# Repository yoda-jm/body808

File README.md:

# Body808

Wearable body percussion: piezo sensors on the feet, chest, legs and hands turn
body hits into MIDI drum notes, sent by radio to a sampler that plays beatbox
sounds.

```
piezo pads ──> protection board ──> Arduino Mega ──> MIDI OUT ──> WIDI Master ~~BLE~~> PC ──> Hydrogen (beatbox kit)
(on the body)   (keeps the Mega alive)  (hit detection)   (DIN-5)    (Bluetooth MIDI)        (or USB cable for testing)
```

Each input plays one fixed sound. Where a pad goes on the body is up to you: plug
it into the input of the sound you want it to play.

| Pin | Sound | MIDI note | Suggested placement |
|-----|-------|-----------|---------------------|
| A0 | kick | 36 | foot (heel stomp) |
| A1 | snare | 38 | leg / thigh |
| A2 | hihat | 42 | other leg |
| A3 | bass | 35 | chest |
| A4 | clap | 39 | hand |
| A5 | openhat | 46 | other hand |

Notes follow the General MIDI drum map, so any drum sampler works out of the box.

> **Never wire a piezo directly to an analog pin.** A stomp produces tens of volts;
> the pin tolerates −0.5 … 5.5 V. Each input needs the 4-part protection circuit
> described in [docs/hardware.md](docs/hardware.md).

## Documentation

- [docs/hardware.md](docs/hardware.md): protection circuit, parts list, building and
  testing the board, making the pads, power and safety, MIDI DIN out
- [docs/parts.md](docs/parts.md): shopping list with links (amazon.fr searches)
- [docs/firmware.md](docs/firmware.md): output modes, pad settings, calibration, tuning
- [docs/sampler.md](docs/sampler.md): getting MIDI into the PC, Hydrogen setup, making
  the beatbox kit, latency
- [docs/simulation.md](docs/simulation.md): simulated hits through 7 board
  configurations (schematics, waveforms, detection), pros and cons of each, and the
  firmware's retrigger tuning
- [sim/README.md](sim/README.md): the simulation's models, sources and how to run it
- [hardware/shield/README.md](hardware/shield/README.md): the PCB that stacks on the Mega
  (8 jacks, MIDI OUT, knob): schematic, how to read the board, ordering it from JLCPCB

## Simulation

The protection board and the hit detector were simulated in ngspice before building
([docs/simulation.md](docs/simulation.md)): a piezo disc model with the real discs'
values, ~60 hits per board configuration from soft to 200 V, and the firmware's
detector replayed on every simulated pin voltage.

- **The pin is safe**: at most 131 µA into the Mega's own protection diodes on a 200 V
  hit (budget 0.5 mA), with the 1N4733A zener.
- **One note per hit**, in every hit shape and every configuration tried.
- **Velocity only works for small signals as built**: 0.2–3 V across the disc. If
  your pads give more (check with `CALIBRATE`), a 100 nF capacitor across the disc
  and R1 = 100 kΩ moves the window to 1–16 V.
- **Retrigger tuning**: `RETRIGGER_RATIO` 0.5 → 0.25 and `DECAY_US` 80 → 50 ms, so a
  soft hit right after a loud one is no longer lost, without ghost notes.

```
python3 sim/run.py        # sweeps: stress, tolerances, ringing, transfer
python3 sim/report.py     # docs/simulation.md figures, per configuration
python3 sim/tuning.py     # firmware retrigger settings
```

## Quick start

1. Build the protection board and **check it with a multimeter before connecting it**
   ([hardware.md](docs/hardware.md#check-before-plugging-into-the-mega)).
2. Upload with `CALIBRATE 1`, set each pad's `threshold`/`maxLevel` from the Serial
   Plotter ([firmware.md](docs/firmware.md#calibration-procedure)).
3. Upload with `CALIBRATE 0` and `MIDI_MODE_DISPLAY`, check hits in the Serial Monitor.
4. Switch to `MIDI_MODE_USB_SERIAL`, run the bridge, play GMRockKit in Hydrogen
   ([sampler.md](docs/sampler.md)).
5. Record beatbox samples, build the kit with `tools/make_hydrogen_kit.py`.
6. Switch to `MIDI_MODE_SERIAL`, plug the WIDI Master into the MIDI OUT socket, pair it
   with the PC ([sampler.md](docs/sampler.md#radio-cme-widi-master)), run on battery.

## Files

```
body808.ino                    firmware (Arduino Mega 2560)
tools/serial_midi_bridge.py    USB/radio serial port -> ALSA MIDI port
tools/make_hydrogen_kit.py     samples/ folder -> Hydrogen drumkit
sim/                           ngspice models, sweeps, firmware replay and tuning
docs/                          documentation and schematics (SVG)
hardware/shield/               KiCad shield PCB + schematic, generated by build_shield.py
attic/                         the original Blink/MIDI test sketch
```

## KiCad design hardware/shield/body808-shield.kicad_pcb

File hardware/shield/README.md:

# body808 shield

A board that plugs on top of the Arduino Mega 2560 and replaces the breadboard. It has
8 protected drum inputs on side-entry 3.5 mm jacks, the MIDI OUT socket for the WIDI
Master, and a flat connector for the sensitivity knob. It overhangs the Mega by 17 mm on
the digital-pin side, so that every connector sits on one edge and all cables leave on
the same side.

## How it stacks

Both boards stay the right way up: the shield sits on top of the Mega, and the pin
headers under it plug into the Mega's sockets. The jacks and the MIDI socket are on the
part that overhangs the Mega.

The second drawing shows the alternative with stackable headers on top, which would let
the factory solder everything in its cheaper one-sided service. In November 2026 JLCPCB
had no stackable header in stock, so the board keeps the headers underneath.
`stacking.py` draws this picture.

## Schematic

To print it, use [body808-shield-schematic.pdf](body808-shield-schematic.pdf). To open it in KiCad, open
`body808-shield.kicad_pro`: the schematic and the board are one KiCad project, linked
part by part. Every check (`make_fab.sh`) runs KiCad's schematic-parity test, which
fails if the board and the schematic disagree on a single part, value or connection.

## How to read the drawing

**Everything is on the top side**, ground included. The underside has no copper
except the pads of the through-hole parts. Every red line you see on top is a real
connection.

**Lanes:** each jack has its own lane, separated by white lines, laid out like its
schematic:

```
    JACK (on the edge)
      sleeve ●──────────┐
         tip ●──┐       │       right line = GND (from the jack's sleeve and switch pins)
      switch ●──┼───────┤
                ├─[1M]──┤       1M and the zener lie flat: from the signal line to GND
              [10k]     │
                ├[ZENER]┘
               [1k]
                │               left line = signal: tip -> 10k -> 1k
             to A0 ... A7 (header into the Mega)
```

**Ground is one line.** It leaves the Mega's GND pins (J1) at the bottom, runs to the
far left, goes up the left edge, then straight across the top through every jack's
sleeve pin, and on to the MIDI socket. Each lane's GND line drops straight down from it,
marked `GND`, and picks up the jack's switch pin on the way. The knob connector gets its
GND from J1 too, along the bottom edge under the A0–A7 pins.

**When nothing is plugged in:** the jack's switch connects the tip to GND, so an empty
input reads 0 and plays nothing.

**The right part of the board:**

- the MIDI socket in the top-right corner, with R1 and R2 under it;
- 5V coming down from the Mega's 5V pins (J7) to the knob connector at the lower right;
- the two test pads below the knob, 5V and GND.

**Labels:** every line has a short label printed next to it (`GND`, `5V`, `TX1`, `A8`,
`220`, the MIDI pin numbers), instead of a legend block. The title is `body808 v1`.

**What goes into the Mega:** only the pins that carry something.

| Header | Pins used | For |
|--------|-----------|-----|
| J1 (POWER) | GND | ground |
| J3 (A0–A7) | all 8 | one per lane |
| J5 (A8–A15) | A8 | knob |
| J6 (comms) | TX1 (pin 18) | MIDI |
| J7 (2 pins at the end of the 2×18 header) | 5V | MIDI and knob |

The other pins of J1, J5 and J6 are only there to hold the shield and aren't connected.

## Connectors

| Ref | What | Wiring |
|-----|------|--------|
| J21–J28 | `JACK1`–`JACK8` (PJ-316 mono jacks) | → A0 … A7. Tip (T) = piezo red, sleeve (S) = GND, switch (TN) = GND |
| J10 | MIDI OUT (DIN-5, CUI SDS-50J) | pin 4 → R1 220 Ω → 5V, pin 5 → R2 220 Ω → TX1, pin 2 + shield → GND, pins 1 and 3 unused |
| J11 | `KNOB` (flat JST-XH, 3 pins) | GND / 5V / A8, as printed next to it |
| TP1, TP2 | Test pads, bottom right | 5V and GND, for a multimeter |

**MIDI uses only 3 of the 5 pins**, which is the MIDI standard. The WIDI Master takes
its power from pin 4 (5V through 220 Ω) and pin 2 (GND), so it needs no other supply.

**Each lane** is the protection circuit from [docs/hardware.md](../../docs/hardware.md):

| Part | Value | Position in the lane |
|------|-------|----------------------|
| R1 | 1 MΩ | flat, signal line to GND line |
| R2 | 10 kΩ | in the signal line |
| D1 | 5.1 V zener, 1SMA4733A | flat, cathode band on the signal line |
| R3 | 1 kΩ | in the signal line, then to the Mega pin |

1SMA4733A is the SMD version of the 1 W 1N4733A that the simulation favours.

If real pads turn out to give more than ~3 V
([docs/simulation.md](../../docs/simulation.md)), the 100 nF capacitor can go across
the piezo inside the pad. That's electrically the same place, so the board doesn't need
a spot for it.

**Clearances:**

- **Piezo inputs:** the line from each jack tip to its 10k sees the piezo's spikes
  (50–200 V, well under a millisecond). It keeps at least 0.8 mm from GND copper,
  including the jack's own GND pins.
- **Other tracks:** at least 0.5 mm apart (A0–A7 lines, 5V and TX1).
- **Board edge:** at least 0.75 mm from copper.

**Nothing pokes into the Mega.** Over the Mega's USB socket, power jack and ICSP header
there are no solder joints and no bottom copper. Over the Mega, only the pin headers
and the knob connector's 3 pins go through the board, and nothing tall sits under the
knob connector. The jacks and the MIDI socket are on the overhang.

## Order it (JLCPCB)

The BOM uses LCSC part numbers, so JLCPCB can assemble the board. `fab/` holds the three
files to upload, nothing else.

1. On jlcpcb.com, upload `fab/gerbers-jlcpcb.zip`. The defaults are fine (2 layers,
   1.6 mm). Pick **lead-free HASL**, since the board will be worn.
2. Enable **PCB Assembly**, **Economic**, top side, 2 or 5 boards. Upload
   `fab/bom-jlcpcb.csv` and `fab/cpl-jlcpcb.csv`.
3. The files ask the factory to solder **everything on the top**: the 34 resistors and
   zeners, the 8 jacks, the MIDI socket and the knob connector. The **pin headers are
   left out on purpose**: they sit on the bottom, and a bottom-side part moves the
   order to double-sided assembly (about $60 more). Solder them yourself (see below).
4. **Check the placement preview** before paying:
   - **Zeners D101 … D801:** each lies flat across its lane. The cathode band must be
     on the **left, on the signal line**. A reversed zener gives no protection.
   - **Jacks and MIDI socket:** facing out of the top edge.
   - **Knob connector:** opening toward the right edge.

   Rotate anything that looks wrong in the preview: rotation conventions differ between
   KiCad and JLCPCB.

**Pin headers, by hand:** 4 strips of 8 (J1, J3, J5, J6) and one of 2 (J7, cut from a
strip), 2.54 mm male, plastic **under** the board, soldered from the top. The easy way
to get them straight: push them into the Mega's sockets, put the shield on top,
solder, then lift it off. LCSC C492407 is a strip of 8.

**What it costs** (researched 2026-11-05, USD before shipping and VAT):

| | 2 boards | 5 boards |
|---|---|---|
| Factory solders everything on top (the files as they are) | ~$40 | ~$63 |
| Factory solders only the 34 small parts, you buy and solder the rest | ~$36 | ~$57 |
| Bare boards only, no parts | ~$5 for 5 | |

- **Where it goes:** the MIDI socket ($4.27 each) and the jacks ($0.22 each) are most
  of the parts cost. The assembly setup is about $8 and the stencil $1.50 per order,
  whatever the quantity.
- **Shipping to France:** about $7–9 for the slow options, about $30 by DHL.
- **VAT and duty:** French VAT (20%) is added at checkout. Since July 2026 each EU
  parcel also pays a flat €3 customs duty per goods category, plus a few euros of handling fees.
  JLCPCB collects that at checkout on some shipping routes; on others it's charged on
  delivery.
- **The famous "$2 for 5 boards"** is now only in JLCPCB's desktop app, which runs on
  Windows and macOS (not Linux); on the website it's about $4.
- **Stock:** the MIDI socket (C6216157) and the Kinghelm jack (C5123139) were low (138
  and 272 left). If the jack runs out, the CAX PJ-316 (C50176628) is a drop-in
  replacement.

Bare boards (no assembly) can also come from PCBWay or Aisler (made in Germany, no
customs for the EU) with the same Gerber zip. You then solder the 1206 parts by hand;
that size is easy with a fine tip.

Part numbers, in case one is out of stock: [build_shield.py](build_shield.py) (`LCSC = {...}`).
The jack has a drop-in second source, CAX PJ-316 (C50176628).

## Before plugging it into the Mega

- Put a piece of Kapton or electrical tape on top of the Mega's USB socket. It reaches
  the underside of the shield.
- Do the multimeter checks from
  [docs/hardware.md](../../docs/hardware.md#check-before-plugging-into-the-mega) on each
  lane, measuring at the jack (tip) and the A0 … A7 header pins.
- Once it's on the Mega and powered, check about 5 V between the test pads at the bottom
  right.
- Tap softly first, with `CALIBRATE 1`.

## Firmware for the shield

Three changes in `body808.ino`:

- `pads[]` gets two more lines, for A6 and A7 (`JACK7`, `JACK8`). Pick their sounds from
  the General MIDI drum map (for example 41 low tom, 49 crash).
- `SENSITIVITY_PIN` becomes `A8`; the knob moves there because A6 and A7 are now pads.
- `MIDI_MODE_SERIAL` sends to the MIDI OUT socket (TX1).

## Regenerate

The board is generated by a script; nothing was drawn by hand. To change something,
edit `build_shield.py` and run:

```sh
hardware/shield/make_fab.sh    # board, DRC, Gerbers, BOM, CPL, renders, annotated view
```

- **Needs:** the KiCad Flatpak (`flatpak install --user flathub org.kicad.KiCad`) and
  ImageMagick.
- **3D models:** KiCad has no model for the PJ-316 jack and the SDS-50J socket. The script
  writes simple ones from the datasheet sizes into `3d/`.
- **DRC:** it stops if KiCad's design-rule check finds an error.
- **Checks:** ERC on the schematic, DRC on the board, and schematic parity between the two.
  The script stops at the first one that fails; the reports are in `.work/`.
- **Editing in KiCad:** open `body808-shield.kicad_pro` in KiCad, or the board directly
  (`flatpak run --command=pcbnew org.kicad.KiCad hardware/shield/body808-shield.kicad_pcb`).

**After editing by hand, export with `--no-build`:**

```sh
hardware/shield/make_fab.sh --no-build    # DRC, Gerbers, CPL, renders from the edited board
```

- **Why:** running `build_shield.py` (or `make_fab.sh` without `--no-build`) regenerates
  the board from scratch, which **overwrites manual edits**.
- **What doesn't follow your edits:** the BOM and the schematic only change when parts
  change, and the callouts in `shield-explained.png` use fixed positions.

## Files

| File | What |
|------|------|
| `build_shield.py` | Builds the board, then the schematic from the board's nets |
| `schematic.py` | Draws the schematic (used by `build_shield.py`) |
| `make_fab.sh` | Runs the generator, the checks, and every export |
| `body808-shield.kicad_pro` / `.kicad_pcb` / `.kicad_sch` | The KiCad project (generated) |
| `body808.pretty/`, `body808.kicad_sym` | Footprints and symbols for the parts KiCad lacks: the PJ-316 jack and the SDS-50J socket (generated) |
| `fp-lib-table`, `sym-lib-table` | Tell KiCad where those two libraries are |
| `3d/` | Simple 3D models of the same two parts (generated) |
| `fab/` | The JLCPCB upload: Gerber zip, BOM, placement (generated) |
| `body808-shield-schematic.pdf`, `images/` | Schematic (PDF to print) and pictures for this page (generated) |
| `annotate.py` | Adds the callouts to `images/shield-explained.png` |
| `stacking.py` | Draws the side view `images/shield-stacking.svg` |

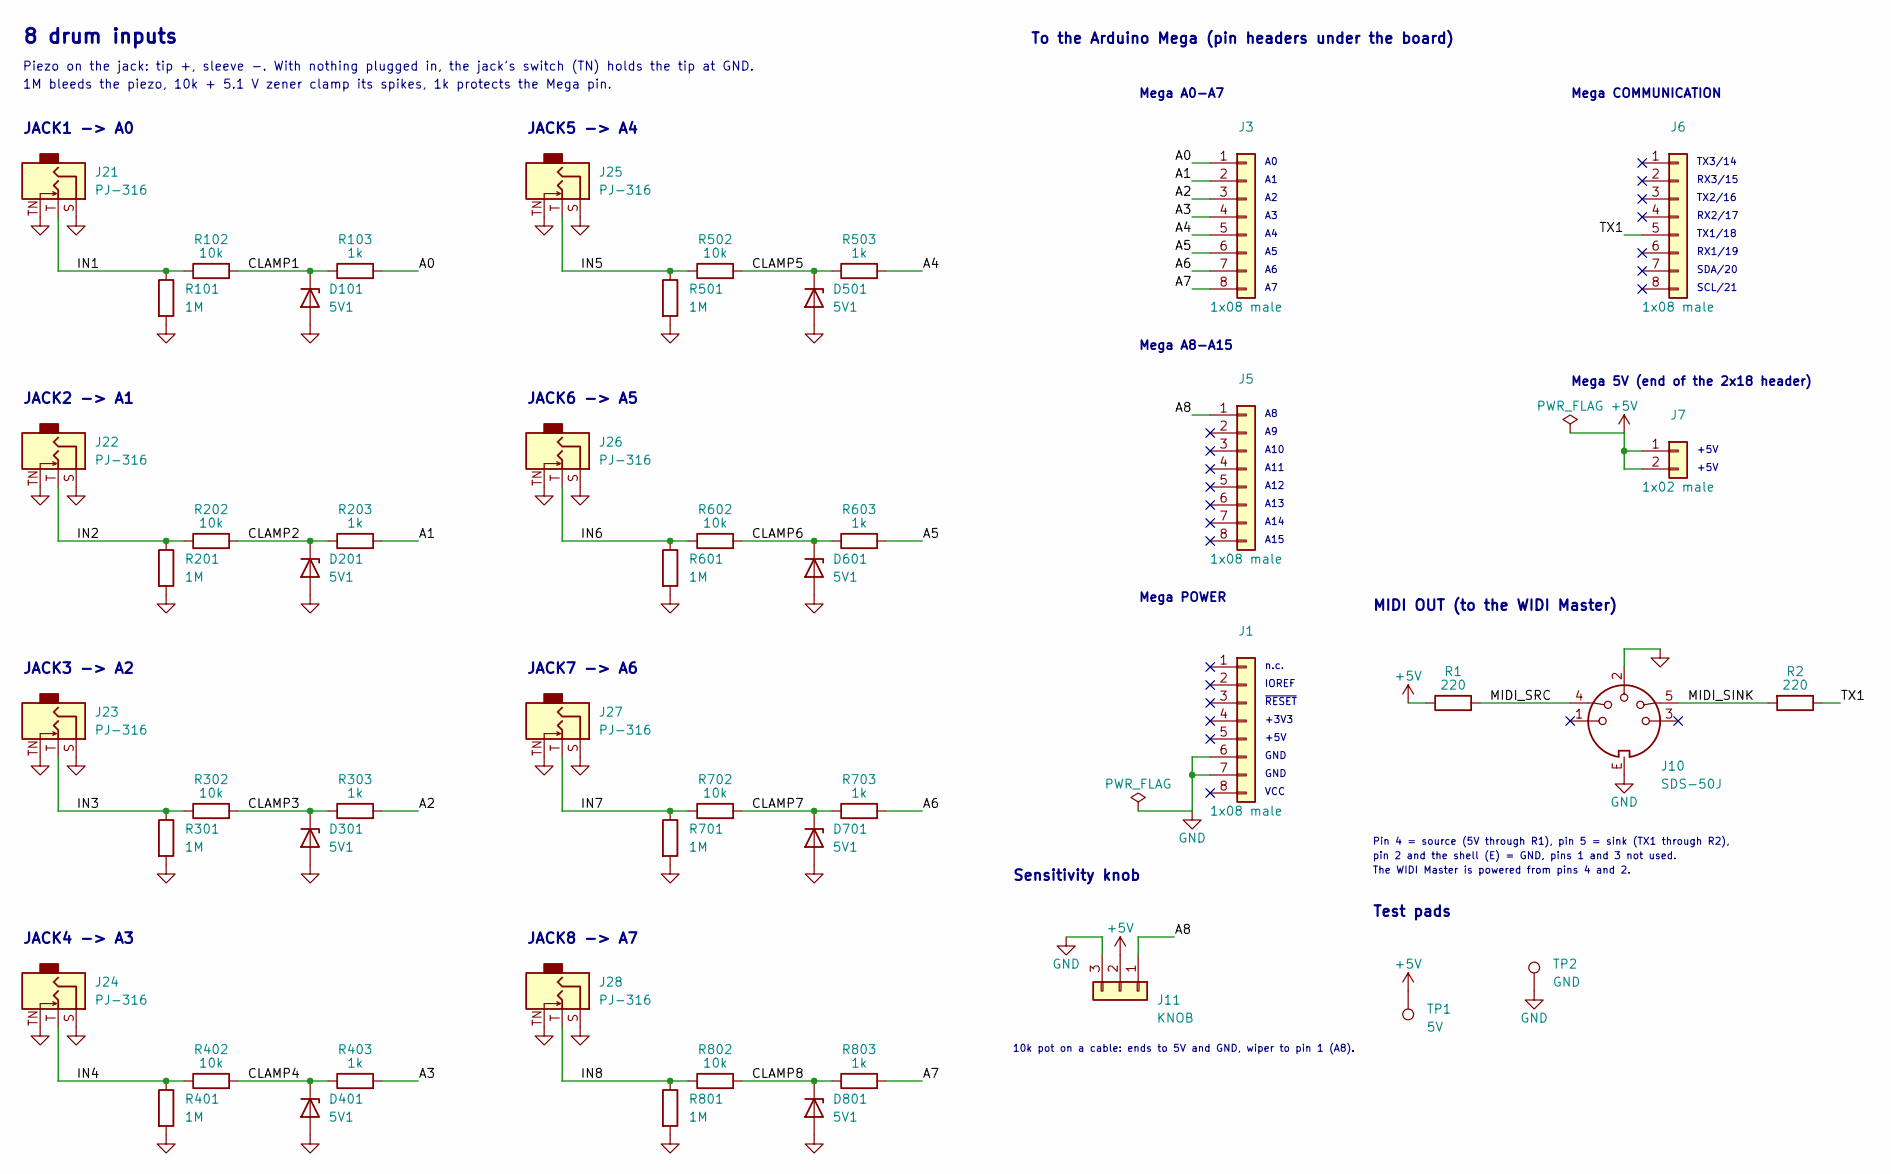
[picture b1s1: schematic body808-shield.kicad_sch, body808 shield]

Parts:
D101, D201, D301, D401, D501, D601, D701, D801: 5V1; D_SMA; LCSC C19077476
J1, J3, J5, J6: 1x08 male; PinHeader_1x08_P2.54mm_Vertical; LCSC C492407
J7: 1x02 male; PinHeader_1x02_P2.54mm_Vertical
J10: SDS-50J; MPN CUI SDS-50J; LCSC C6216157
J11: KNOB; JST_XH_S3B-XH-A_1x03_P2.50mm_Horizontal; LCSC C157928
J21, J22, J23, J24, J25, J26, J27, J28: PJ-316; MPN KH-PJ-316-3P (or CAX PJ-316, C50176628); LCSC C5123139
R1, R2: 220; R_1206_3216Metric; LCSC C17957
R101, R201, R301, R401, R501, R601, R701, R801: 1M; R_1206_3216Metric; LCSC C17927
R102, R202, R302, R402, R502, R602, R702, R802: 10k; R_1206_3216Metric; LCSC C17902
R103, R203, R303, R403, R503, R603, R703, R803: 1k; R_1206_3216Metric; LCSC C4410
TP1: 5V; TestPoint_Pad_D1.5mm
TP2: GND; TestPoint_Pad_D1.5mm

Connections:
+5V: J7.1, J7.2, J11.2, R1.1, TP1.1
/A0: J3.1, R103.2
/A1: J3.2, R203.2
/A2: J3.3, R303.2
/A3: J3.4, R403.2
/A4: J3.5, R503.2
/A5: J3.6, R603.2
/A6: J3.7, R703.2
/A7: J3.8, R803.2
/A8: J5.1, J11.1
/CLAMP1: D101.1 (K), R102.2, R103.1
/CLAMP2: D201.1 (K), R202.2, R203.1
/CLAMP3: D301.1 (K), R302.2, R303.1
/CLAMP4: D401.1 (K), R402.2, R403.1
/CLAMP5: D501.1 (K), R502.2, R503.1
/CLAMP6: D601.1 (K), R602.2, R603.1
/CLAMP7: D701.1 (K), R702.2, R703.1
/CLAMP8: D801.1 (K), R802.2, R803.1
/IN1: J21.T, R101.1, R102.1
/IN2: J22.T, R201.1, R202.1
/IN3: J23.T, R301.1, R302.1
/IN4: J24.T, R401.1, R402.1
/IN5: J25.T, R501.1, R502.1
/IN6: J26.T, R601.1, R602.1
/IN7: J27.T, R701.1, R702.1
/IN8: J28.T, R801.1, R802.1
/MIDI_SINK: J10.5, R2.2
/MIDI_SRC: J10.4, R1.2
/TX1: J6.5, R2.1
GND: D101.2 (A), D201.2 (A), D301.2 (A), D401.2 (A), D501.2 (A), D601.2 (A), D701.2 (A), D801.2 (A), J1.6, J1.7, J10.2, J10.E, J11.3, J21.S, J21.TN, J22.S, J22.TN, J23.S, J23.TN, J24.S, J24.TN, J25.S, J25.TN, J26.S, J26.TN, J27.S, J27.TN, J28.S, J28.TN, R101.2, R201.2, R301.2, R401.2, R501.2, R601.2, R701.2, R801.2, TP2.1

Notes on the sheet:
The WIDI Master is powered from pins 4 and 2.
IOREF
A13
GND
10k pot on a cable: ends to 5V and GND, wiper to pin 1 (A8).
Mega 5V (end of the 2x18 header)
Mega A0-A7
Sensitivity knob
MIDI OUT (to the WIDI Master)
A14
TX3/14
1M bleeds the piezo, 10k + 5.1 V zener clamp its spikes, 1k protects the Mega pin.
Pin 4 = source (5V through R1), pin 5 = sink (TX1 through R2),
JACK6 -> A5
Mega A8-A15
JACK5 -> A4
JACK2 -> A1
SCL/21
n.c.
Mega COMMUNICATION
JACK3 -> A2
~{RESET}
8 drum inputs
+5V
RX3/15
JACK1 -> A0
To the Arduino Mega (pin headers under the board)
A12
pin 2 and the shell (E) = GND, pins 1 and 3 not used.
TX1/18
VCC
A11
Piezo on the jack: tip +, sleeve -. With nothing plugged in, the jack's switch (TN) holds the tip at GND.
A15
+3V3
SDA/20
RX2/17
JACK7 -> A6
Test pads
TX2/16

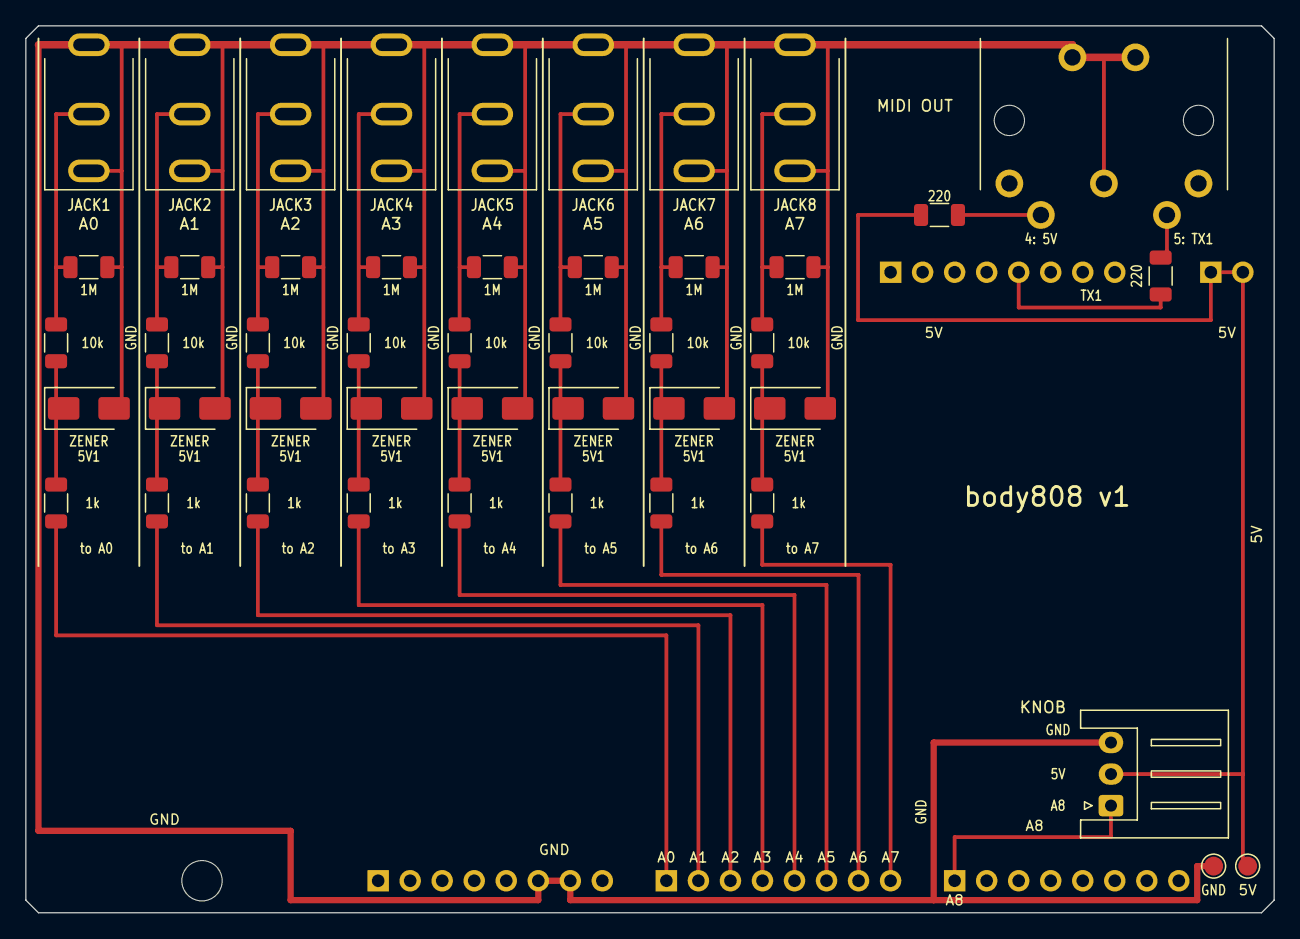
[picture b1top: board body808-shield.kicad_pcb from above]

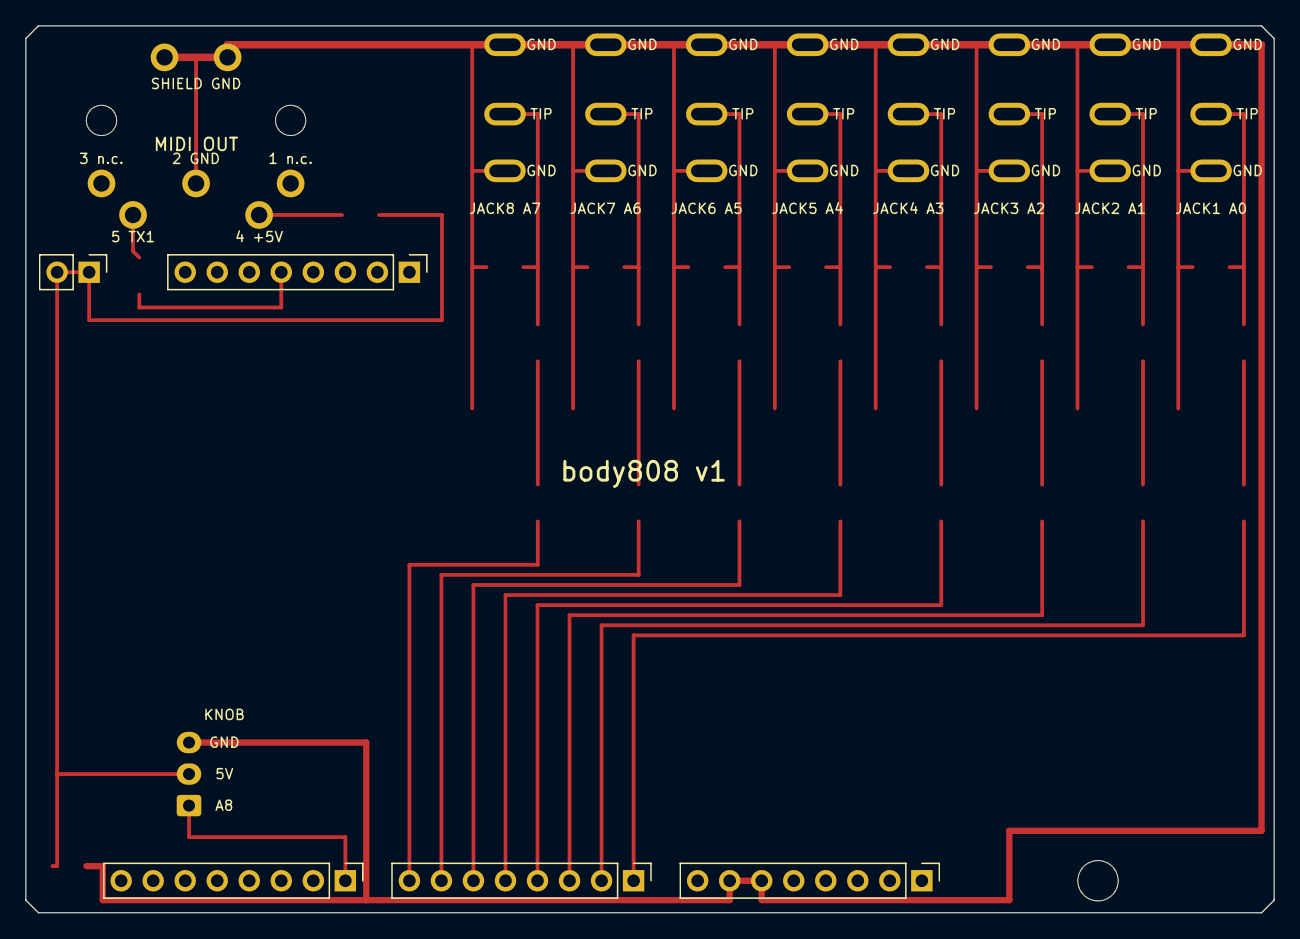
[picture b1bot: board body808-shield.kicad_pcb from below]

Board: 2 copper layers, 99.0 x 70.3 mm, 52 parts (5 on the bottom side), 30 nets.

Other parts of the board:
MH2: M3; MountingHole_3.2mm_M3

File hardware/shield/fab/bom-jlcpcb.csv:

Comment,Designator,Footprint,LCSC Part #
10k,"R102,R202,R302,R402,R502,R602,R702,R802",R_1206_3216Metric,C17902
1M,"R101,R201,R301,R401,R501,R601,R701,R801",R_1206_3216Metric,C17927
1k,"R103,R203,R303,R403,R503,R603,R703,R803",R_1206_3216Metric,C4410
220,"R1,R2",R_1206_3216Metric,C17957
5V1,"D101,D201,D301,D401,D501,D601,D701,D801",D_SMA,C19077476
KNOB,J11,JST_XH_S3B-XH-A_1x03_P2.50mm_Horizontal,C157928
PJ-316,"J21,J22,J23,J24,J25,J26,J27,J28",PJ-316,C5123139
SDS-50J,J10,SDS-50J,C6216157
